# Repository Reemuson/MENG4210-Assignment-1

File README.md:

<h1 align="center">INPUT PROTECTION</h1>

<p align="center" width="100%">
  
</p>

***

<p align="center">
  
&nbsp; &nbsp; &nbsp; &nbsp;
  
</p>

***

## SPECIFICATIONS

| Parameter | Value | 
| --- | --- |
| Dimensions | 80.0 × 40.0 mm |

***

## DIRECTORY STRUCTURE

    .
    ├─ Computations       # Misc calculations
    ├─ HTML               # HTML files for generated webpage
    ├─ Images             # Pictures and renders
    │
    ├─ kibot_resources    # External resources for KiBot
    │  ├─ colors          # Color theme for KiCad
    │  ├─ fonts           # Fonts used in the project
    │  ├─ scripts         # External scripts used with KiBot
    │  └─ templates       # Templates for KiBot generated reports
    │
    ├─ kibot_yaml         # KiBot YAML config files
    ├─ KiRI               # KiRI (PCB diff viewer) files
    │
    ├─ lib                # KiCad footprint and symbol libraries
    │  ├─ 3d_models       # Component 3D models
    │  ├─ lib_fp          # Footprint libraries
    │  └─ lib_sym         # Symbol libraries
    │
    ├─ Logos              # Logos
    │
    ├─ Manufacturing      # Assembly and fabrication documents
    │  ├─ Assembly        # Assembly documents (BoM, pos, notes)
    │  │
    │  └─ Fabrication     # Fabrication documents (ZIP, notes)
    │     ├─ Drill Tables # CSV drill tables
    │     └─ Gerbers      # Gerbers
    │
    ├─ Report             # Reports for ERC/DRC
    ├─ Schematic          # PDF of schematic
    ├─ Templates          # Title block templates
    ├─ Testing
    │  └─ Testpoints      # Testpoints tables      
    │
    └─ Variants           # Outputs for assembly variants

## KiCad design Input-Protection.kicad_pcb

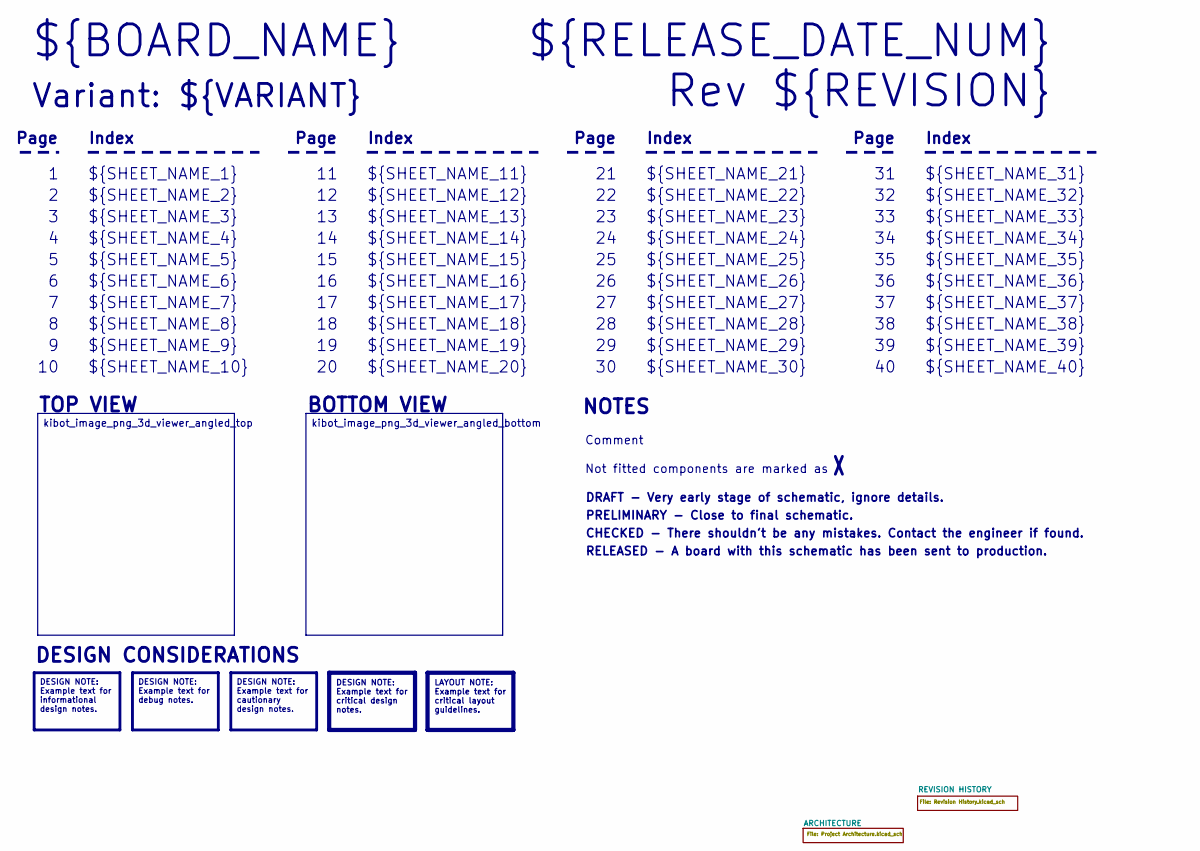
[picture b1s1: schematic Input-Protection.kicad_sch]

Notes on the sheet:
Variant: ${VARIANT}
RELEASED - A board with this schematic has been sent to production.
${SHEET_NAME_24}
Index
Page
PRELIMINARY - Close to final schematic.
${SHEET_NAME_22}
DRAFT - Very early stage of schematic, ignore details.
${SHEET_NAME_12}
${SHEET_NAME_8}
${SHEET_NAME_2}
${SHEET_NAME_5}
${SHEET_NAME_20}
${SHEET_NAME_23}
${RELEASE_DATE_NUM}
${SHEET_NAME_35}
Not fitted components are marked as
${SHEET_NAME_11}
${SHEET_NAME_6}
${SHEET_NAME_37}
${SHEET_NAME_26}
${SHEET_NAME_36}
Rev ${REVISION}
${SHEET_NAME_15}
CHECKED - There shouldn't be any mistakes. Contact the engineer if found.
BOTTOM VIEW
${SHEET_NAME_14}
${SHEET_NAME_21}
${SHEET_NAME_17}
${SHEET_NAME_18}
${SHEET_NAME_7}
${SHEET_NAME_31}
${BOARD_NAME}
NOTES
${SHEET_NAME_40}
${SHEET_NAME_39}
${SHEET_NAME_32}
${SHEET_NAME_1}
${SHEET_NAME_9}
${SHEET_NAME_38}

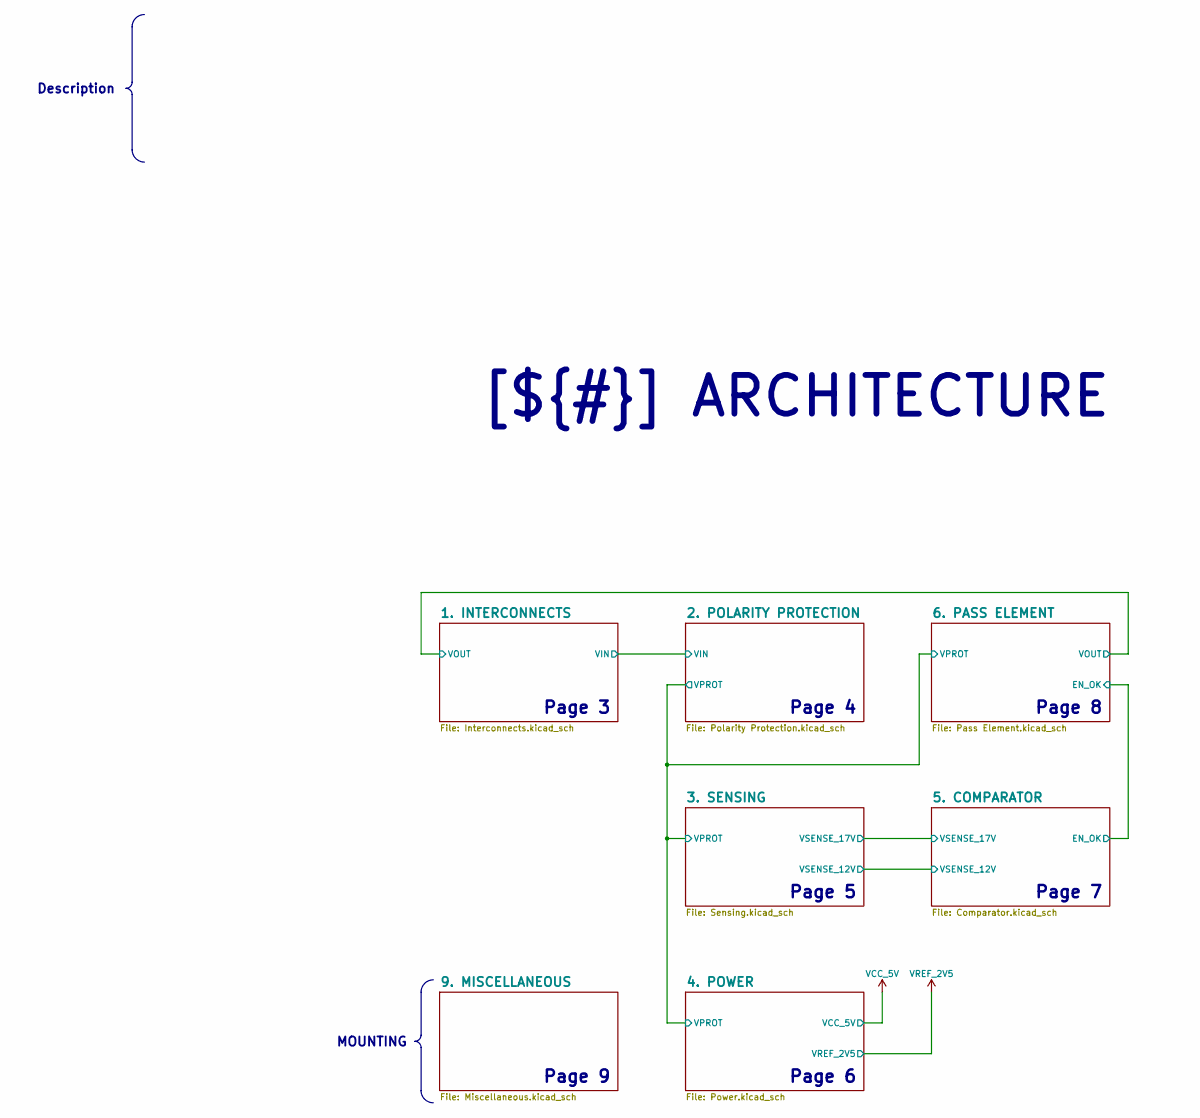
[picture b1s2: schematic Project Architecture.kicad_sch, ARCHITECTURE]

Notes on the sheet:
Page 7
Page 9
Page 3
Page 5
Page 8
Page 6
Page 4
Description
MOUNTING
[${#}] ${TITLE}

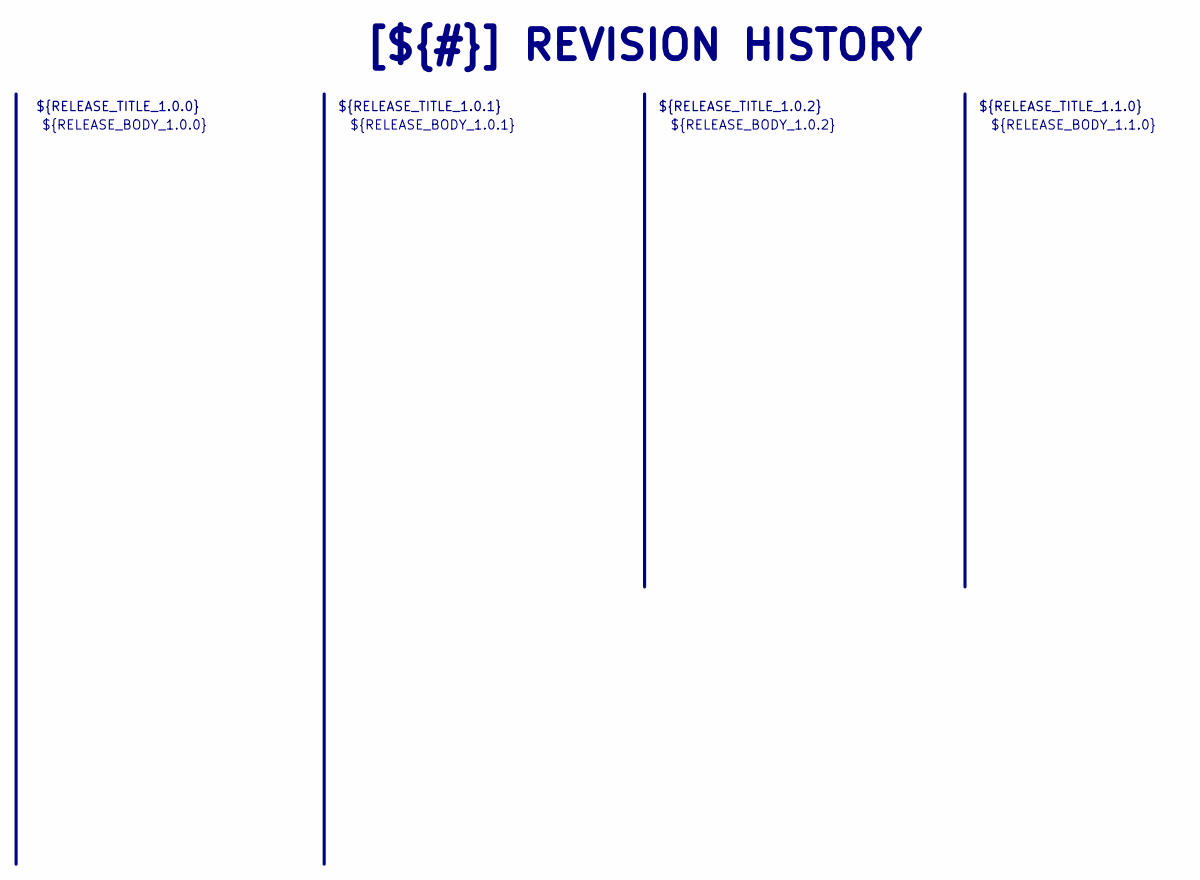
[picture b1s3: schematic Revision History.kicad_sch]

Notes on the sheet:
${RELEASE_BODY_1.1.0}
[${#}] ${TITLE}
${RELEASE_BODY_1.0.0}
${RELEASE_TITLE_1.0.2}
${RELEASE_BODY_1.0.2}
${RELEASE_BODY_1.0.1}
${RELEASE_TITLE_1.0.0}
${RELEASE_TITLE_1.0.1}
${RELEASE_TITLE_1.1.0}

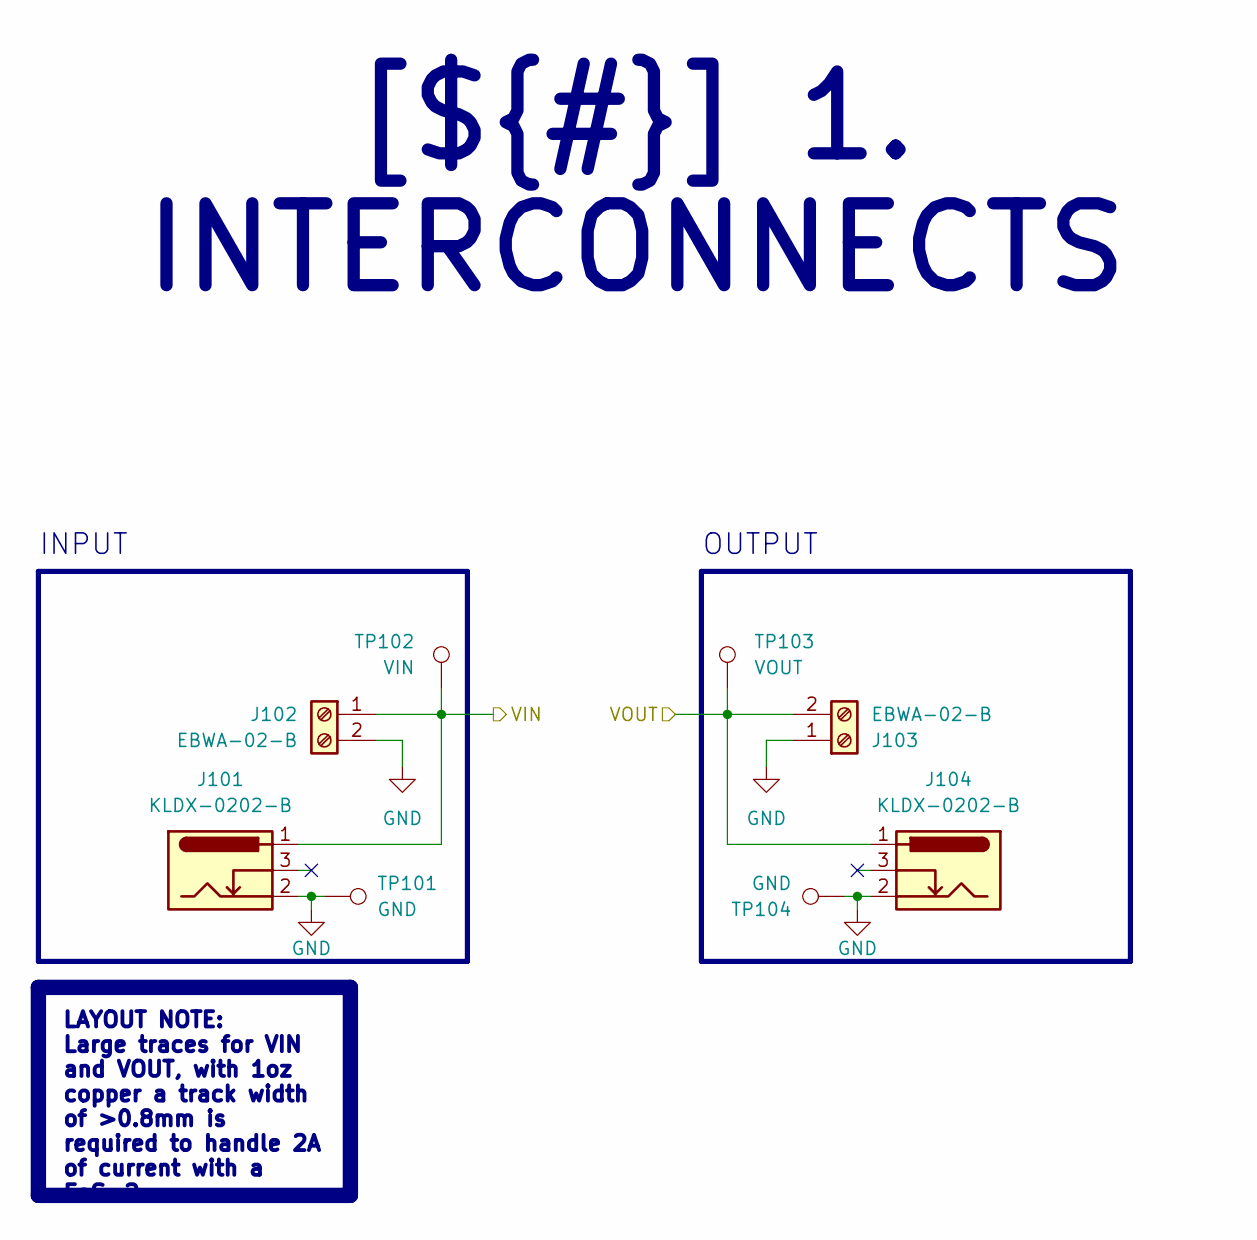
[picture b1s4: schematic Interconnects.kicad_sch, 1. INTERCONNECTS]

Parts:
J101: KLDX-0202-B; BarrelJack_Kycon_KLDX-0202-xC_Horizontal; MPN KLDX-0202-B
J102: EBWA-02-B; TerminalBlock_Phoenix_MKDS-1-2-3.81_1x02_P3.81mm_Horizontal; MPN EBWA-02-B
J103: EBWA-02-B; TerminalBlock_Phoenix_MKDS-1-2-3.81_1x02_P3.81mm_Horizontal
J104: KLDX-0202-B; BarrelJack_Kycon_KLDX-0202-xC_Horizontal
TP101, TP104: GND; TestPoint_THTPad_1.5x1.5mm_Drill0.7mm
TP102: VIN; TestPoint_Pad_D1.0mm
TP103: VOUT; TestPoint_Pad_D1.0mm

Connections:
/ARCHITECTURE/1. INTERCONNECTS/VIN: J101.1, J102.1, TP102.1; also elsewhere on the board
/ARCHITECTURE/1. INTERCONNECTS/VOUT: J103.2, J104.1, TP103.1; also elsewhere on the board
GND: J101.2, J102.2, J103.1, J104.2, TP101.1, TP104.1; also elsewhere on the board

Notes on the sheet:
INPUT
OUTPUT
LAYOUT NOTE: Large traces for VIN and VOUT, with 1oz copper a track width of >0.8mm is required to handle 2A of current with a FoS=2.
[${#}] ${TITLE}

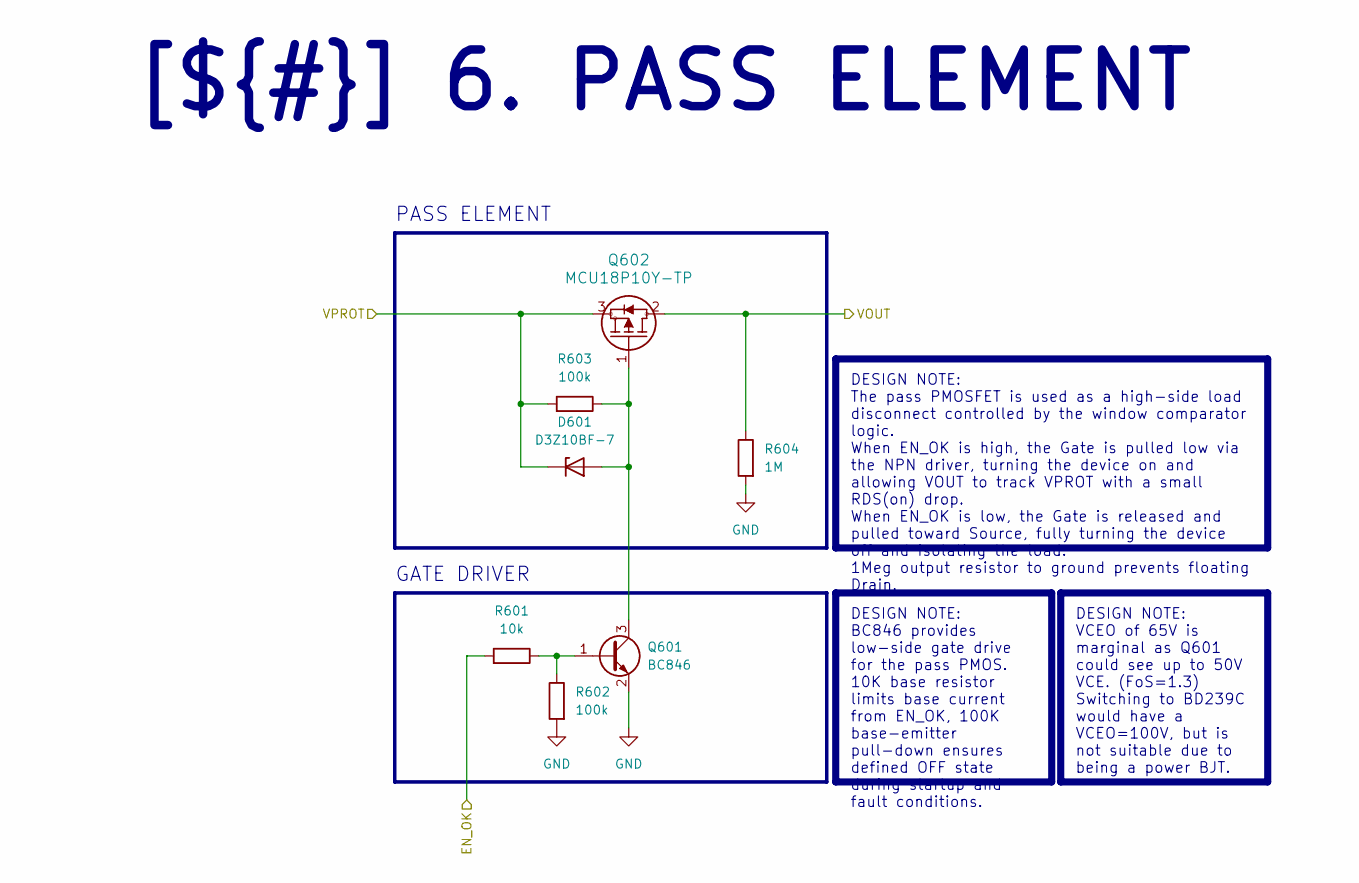
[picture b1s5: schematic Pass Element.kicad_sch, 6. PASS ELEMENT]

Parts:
D601: D3Z10BF-7; D_SOD-323_HandSoldering; MPN D3Z10BF-7
Q601: BC846; SOT-23; MPN BC846
Q602: MCU18P10Y-TP; DPAK_MCC; MPN MCU18P10Y-TP
R601: 10k; R_1206_3216Metric_Pad1.30x1.75mm_HandSolder
R602, R603: 100k; R_1206_3216Metric_Pad1.30x1.75mm_HandSolder
R604: 1M; R_1206_3216Metric_Pad1.30x1.75mm_HandSolder

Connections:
/ARCHITECTURE/1. INTERCONNECTS/VOUT: Q602.2, R604.1; also elsewhere on the board
/ARCHITECTURE/2. POLARITY PROTECTION/VPROT: D601.1 (K), Q602.3, R603.2; also elsewhere on the board
/ARCHITECTURE/5. COMPARATOR/EN_OK: R601.2; also elsewhere on the board
GND: Q601.2 (E), R602.2, R604.2; also elsewhere on the board
unnamed: D601.2 (A), Q601.3 (C), Q602.1, R603.1
unnamed: Q601.1 (B), R601.1, R602.1

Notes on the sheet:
PASS ELEMENT
GATE DRIVER
DESIGN NOTE: The pass PMOSFET is used as a high-side load disconnect controlled by the window comparator logic. When EN_OK is high, the Gate is pulled low via the NPN driver, turning the device on and allowing VOUT to track VPROT with a small RDS(on) drop. When EN_OK is low, the Gate is released an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
DESIGN NOTE: VCEO of 65V is marginal as Q601 could see up to 50V VCE. (FoS=1.3) Switching to BD239C would have a VCEO=100V, but is not suitable due to being a power BJT.
DESIGN NOTE: BC846 provides low-side gate drive for the pass PMOS. 10K base resistor limits base current from EN_OK, 100K base-emitter pull-down ensures defined OFF state during startup and fault conditions.
[${#}] ${TITLE}

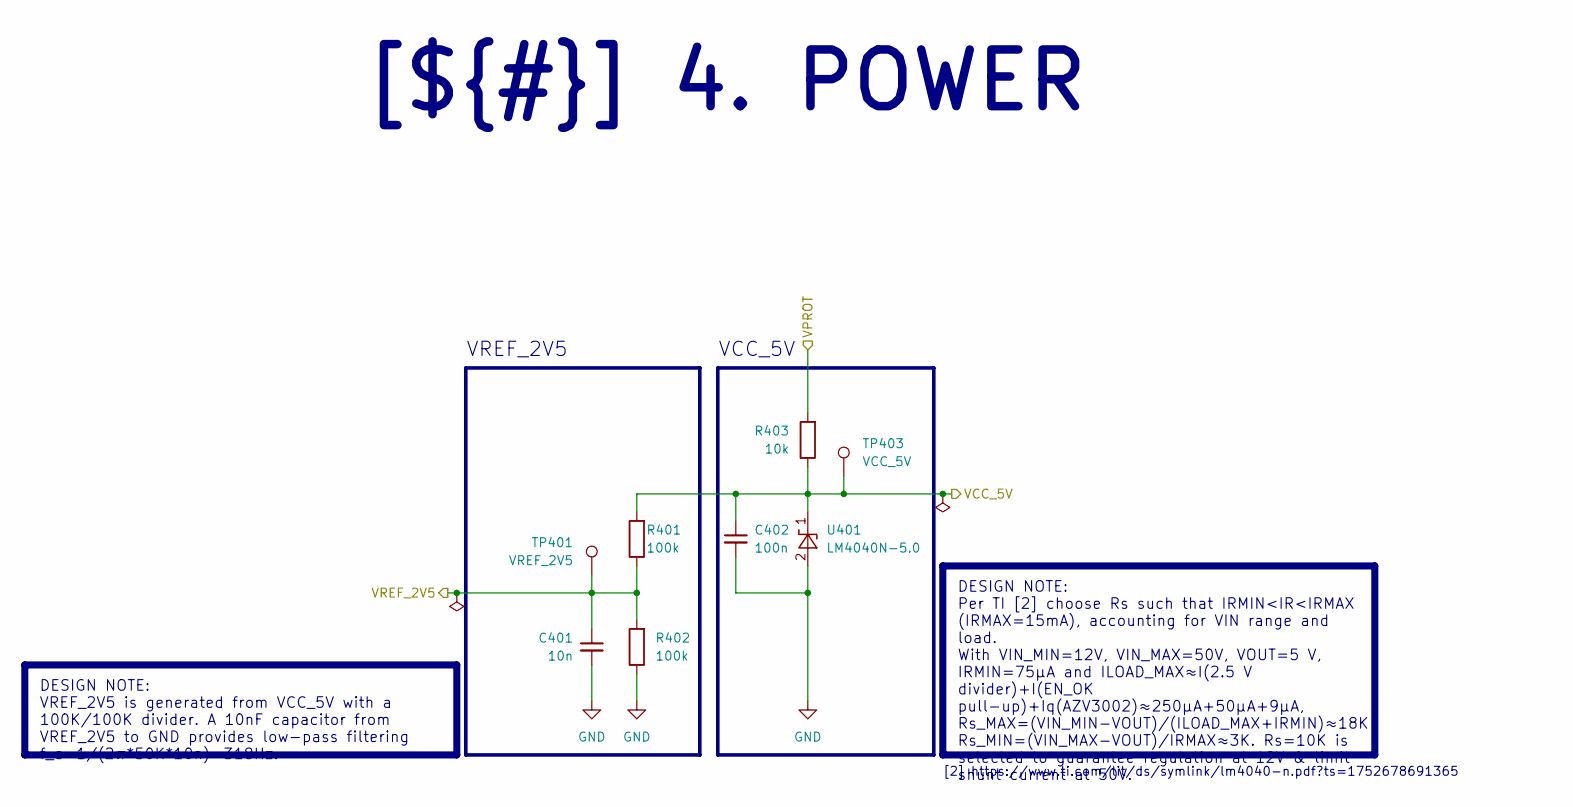
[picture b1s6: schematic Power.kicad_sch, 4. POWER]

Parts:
C401: 10n; C_0603_1608Metric_Pad1.08x0.95mm_HandSolder; Voltage_Rating 50V; Tolerance 10%; MPN C1608X7R1H103KT
C402: 100n; C_0603_1608Metric_Pad1.08x0.95mm_HandSolder; Voltage_Rating 16V; Tolerance 10%; MPN C1608X7R1C104KT
R401, R402: 100k; R_1206_3216Metric_Pad1.30x1.75mm_HandSolder
R403: 10k; R_1206_3216Metric_Pad1.30x1.75mm_HandSolder
TP401: VREF_2V5; TestPoint_Pad_D1.0mm
TP403: VCC_5V; TestPoint_Pad_D1.0mm
U401: LM4040N-5.0; SOT-23; MPN LM4040CIM3-5.0/NOPB

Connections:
/ARCHITECTURE/2. POLARITY PROTECTION/VPROT: R403.2; also elsewhere on the board
GND: C401.2, C402.2, R402.1, U401.2 (A); also elsewhere on the board
VCC_5V: C402.1, R401.2, R403.1, TP403.1, U401.1 (K); also elsewhere on the board
VREF_2V5: C401.1, R401.1, R402.2, TP401.1; also elsewhere on the board

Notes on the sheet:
VREF_2V5
VCC_5V
[2] https://www.ti.com/lit/ds/symlink/lm4040-n.pdf?ts=1752678691365
DESIGN NOTE: VREF_2V5 is generated from VCC_5V with a 100K/100K divider. A 10nF capacitor from VREF_2V5 to GND provides low-pass filtering f_c=1/(2π*50K*10n)=318Hz.
DESIGN NOTE: Per TI [2] choose Rs such that IRMIN<IR<IRMAX (IRMAX=15mA), accounting for VIN range and load. With VIN_MIN=12V, VIN_MAX=50V, VOUT=5 V, IRMIN=75µA and ILOAD_MAX≈I(2.5 V divider)+I(EN_OK pull-up)+Iq(AZV3002)≈250µA+50µA+9µA, Rs_MAX=(VIN_MIN−VOUT)/(ILOAD_MAX+IRMIN)≈18K Rs_MIN=(VIN_MAX−VOU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
[${#}] ${TITLE}

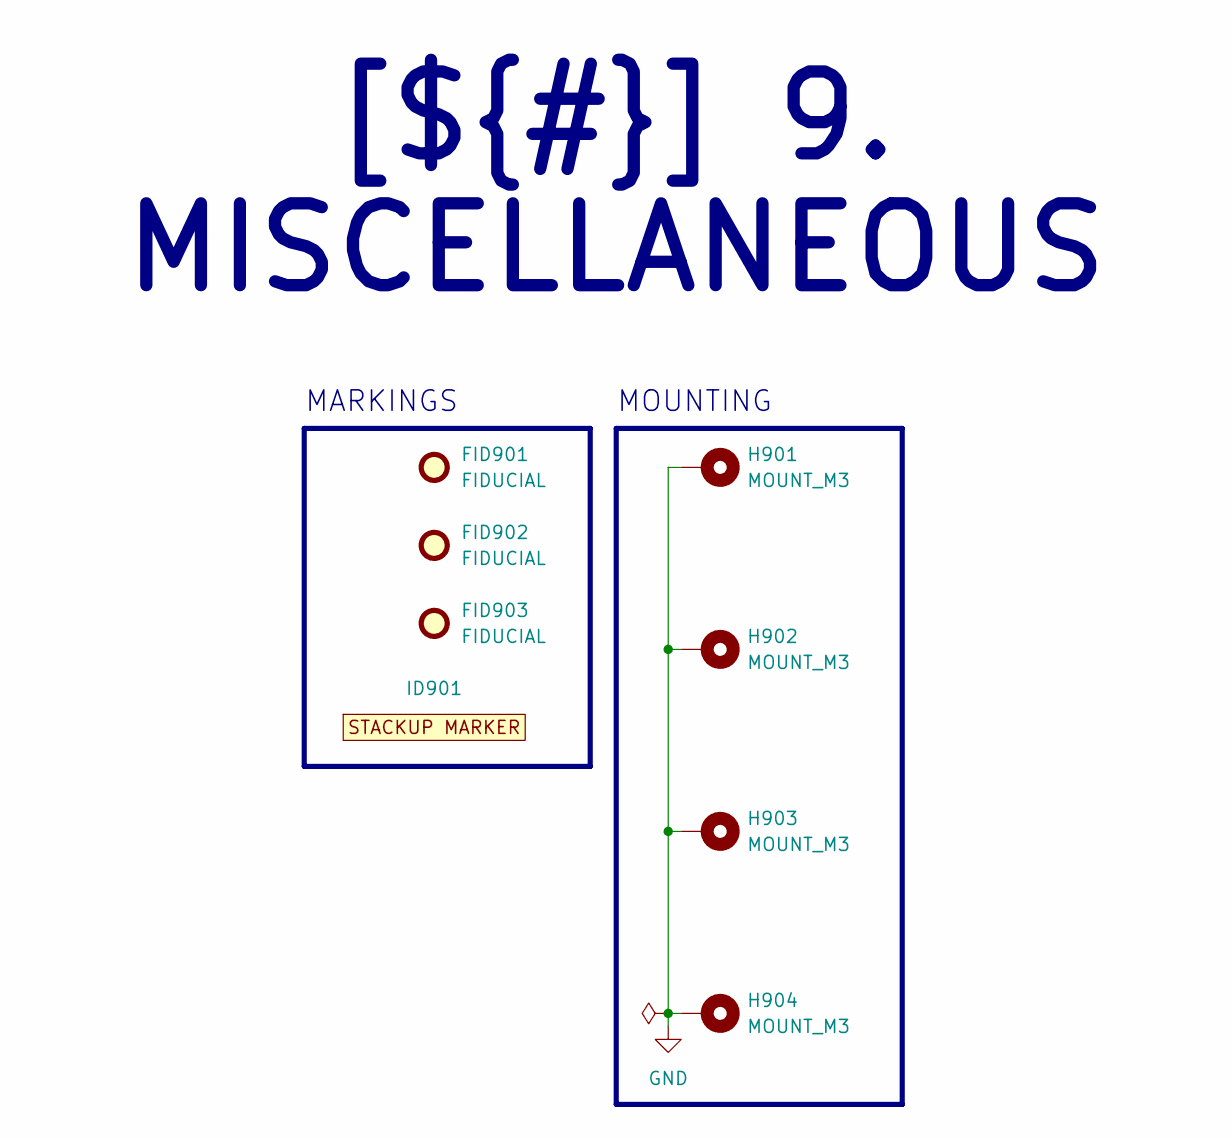
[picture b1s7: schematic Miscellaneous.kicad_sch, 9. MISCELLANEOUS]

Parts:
FID901, FID902, FID903: FIDUCIAL; Fiducial_Cross_0.5mm_Mask2mm
H901, H902, H903, H904: MOUNT_M3; MountingHole_3.2mm_M3_ISO7380_Pad
ID901: BOARD_STACKUP_MARKER; STACKUP_ID_2L_SML

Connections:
GND: H901.1, H902.1, H903.1, H904.1; also elsewhere on the board

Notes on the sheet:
MOUNTING
MARKINGS
[${#}] ${TITLE}

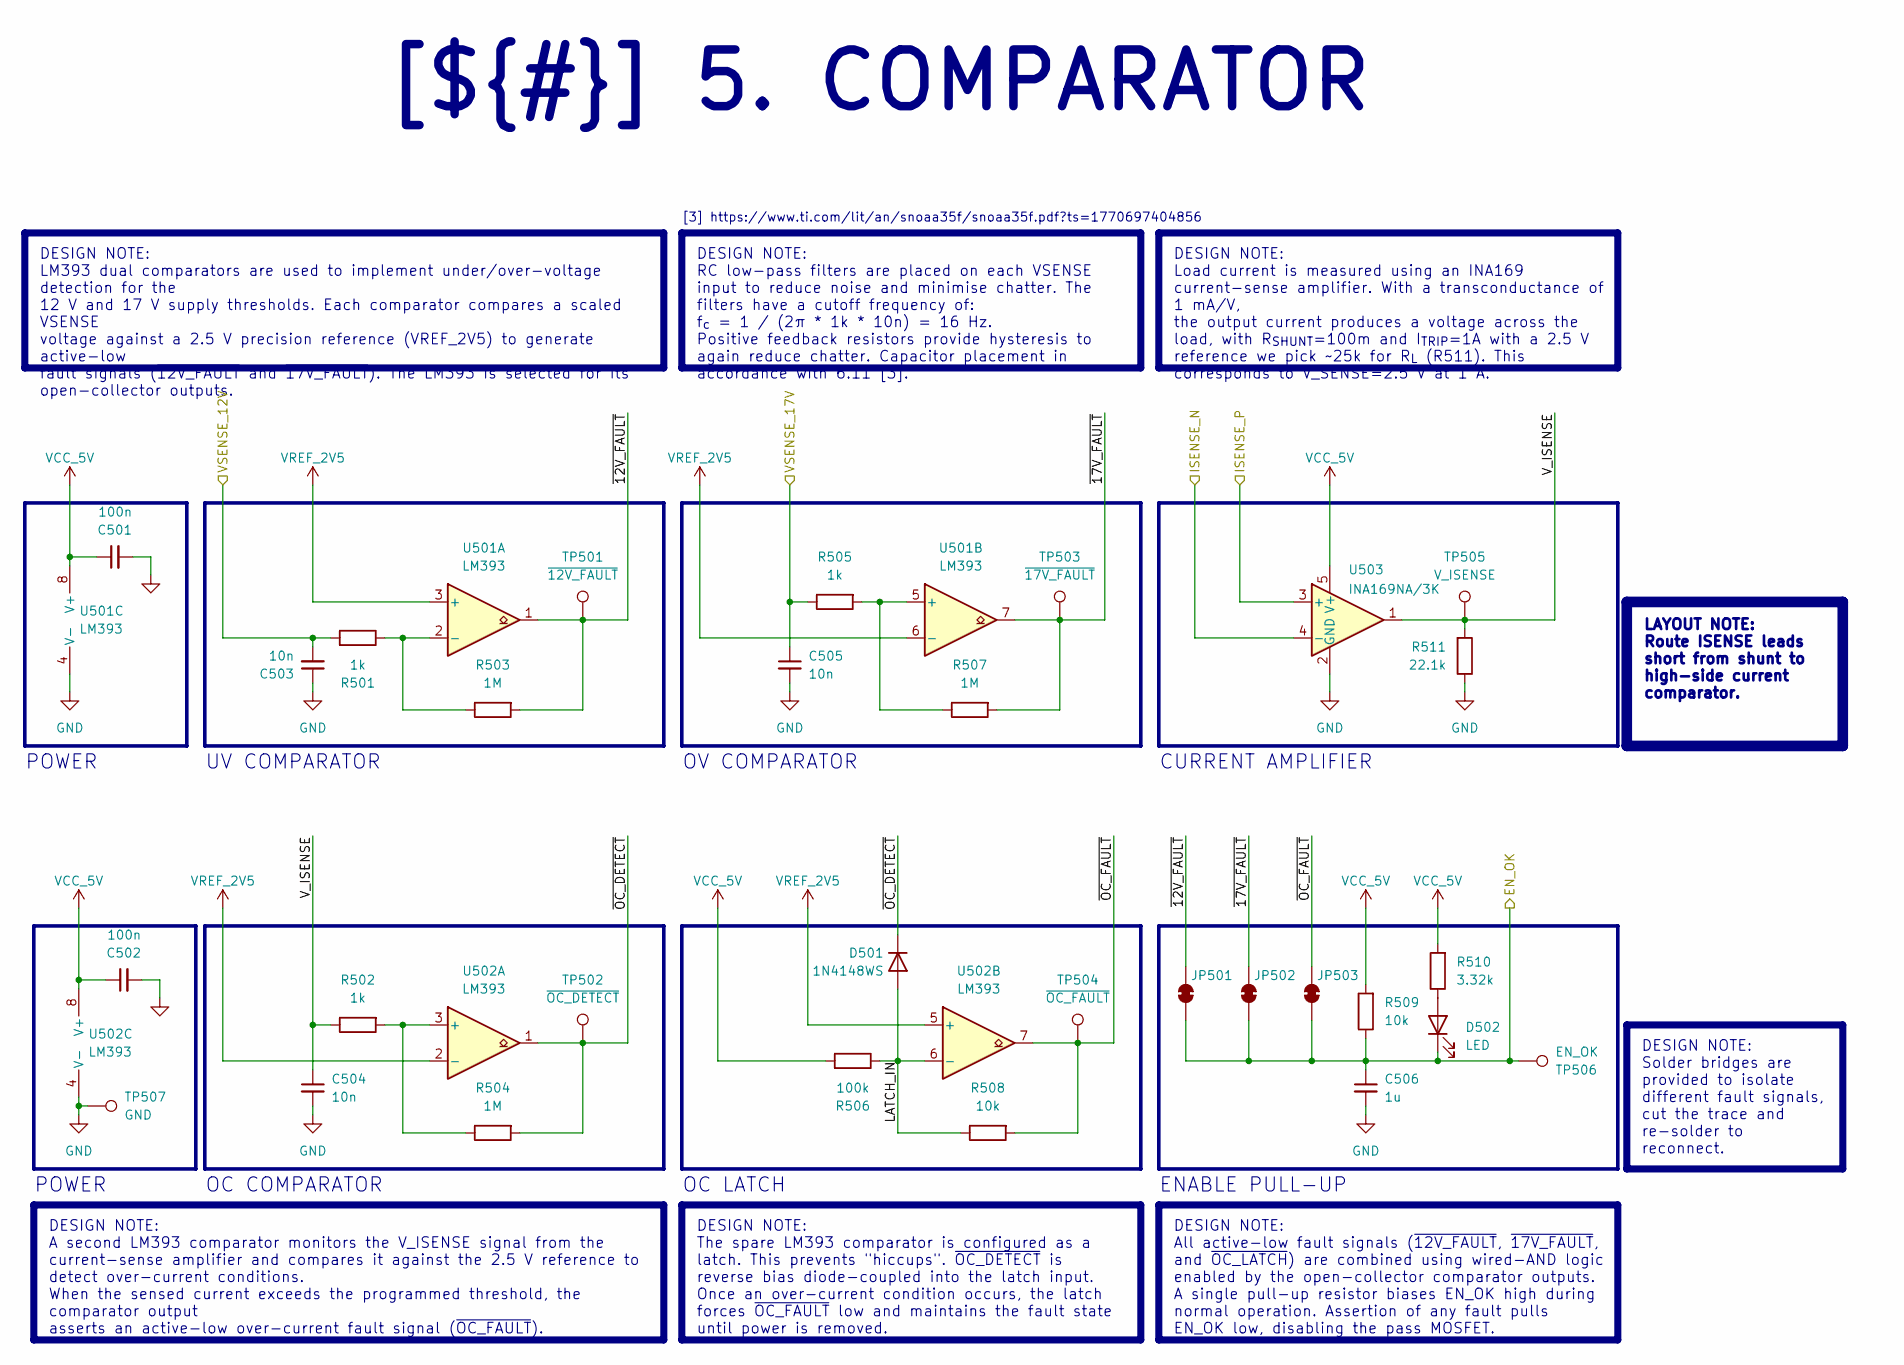
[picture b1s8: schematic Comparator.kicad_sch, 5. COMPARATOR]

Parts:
C501, C502: 100n; C_0603_1608Metric_Pad1.08x0.95mm_HandSolder; Voltage_Rating 16V; Tolerance 10%; MPN C1608X7R1C104KT
C503, C504, C505: 10n; C_0603_1608Metric_Pad1.08x0.95mm_HandSolder; Voltage_Rating 50V; Tolerance 10%; MPN C1608X7R1H103KT
C506: 1u; C_0603_1608Metric_Pad1.08x0.95mm_HandSolder; Voltage_Rating 6.3V; Tolerance 10%; MPN C1608X5R0J105KT
D501: 1N4148WS; D_SOD-323; MPN 1N4148WS
D502: LED; LED_0805_2012Metric_Pad1.15x1.40mm_HandSolder; MPN LTST-C170KRKT
JP501, JP502, JP503: SolderJumper_2_Bridged; SolderJumper-2_P1.3mm_Bridged_Pad1.0x1.5mm
R501, R502, R505: 1k; R_1206_3216Metric_Pad1.30x1.75mm_HandSolder
R503, R504, R507: 1M; R_1206_3216Metric_Pad1.30x1.75mm_HandSolder
R506: 100k; R_1206_3216Metric_Pad1.30x1.75mm_HandSolder
R508, R509: 10k; R_1206_3216Metric_Pad1.30x1.75mm_HandSolder
R510: 3.32k; R_1206_3216Metric_Pad1.30x1.75mm_HandSolder
R511: 22.1k; R_1206_3216Metric_Pad1.30x1.75mm_HandSolder
TP501: ~{12V_FAULT}; TestPoint_Pad_D1.0mm
TP502: ~{OC_DETECT}; TestPoint_Pad_D1.0mm
TP503: ~{17V_FAULT}; TestPoint_Pad_D1.0mm
TP504: ~{OC_FAULT}; TestPoint_Pad_D1.0mm
TP505: V_ISENSE; TestPoint_Pad_D1.0mm
TP506: EN_OK; TestPoint_Pad_D1.0mm
TP507: GND; TestPoint_THTPad_1.5x1.5mm_Drill0.7mm
U501, U502: LM393; SOIC-8_3.9x4.9mm_P1.27mm; MPN LM393ADT
U503: INA169NA/3K; SOT-23-5; MPN INA169NA/3K

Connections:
/ARCHITECTURE/2. POLARITY PROTECTION/VPROT: U503.3 (+); also elsewhere on the board
/ARCHITECTURE/3. SENSING/ISENSE_N: U503.4 (-); also elsewhere on the board
/ARCHITECTURE/3. SENSING/VSENSE_12V: C503.2, R501.2; also elsewhere on the board
/ARCHITECTURE/3. SENSING/VSENSE_17V: C505.1, R505.1; also elsewhere on the board
/ARCHITECTURE/5. COMPARATOR/EN_OK: C506.1, D502.1 (K), JP501.1 (A), JP502.1 (A), JP503.1 (A), R509.1, TP506.1; also elsewhere on the board
/ARCHITECTURE/5. COMPARATOR/LATCH_IN: D501.2 (A), R506.1, R508.1, U502.6 (-)
/ARCHITECTURE/5. COMPARATOR/V_ISENSE: C504.1, R502.1, R511.2, TP505.1, U503.1
/ARCHITECTURE/5. COMPARATOR/~12V_FAULT: JP501.2 (B), R503.2, TP501.1, U501.1
/ARCHITECTURE/5. COMPARATOR/~17V_FAULT: JP502.2 (B), R507.2, TP503.1, U501.7
/ARCHITECTURE/5. COMPARATOR/~OC_DETECT: D501.1 (K), R504.2, TP502.1, U502.1
/ARCHITECTURE/5. COMPARATOR/~OC_FAULT: JP503.2 (B), R508.2, TP504.1, U502.7
GND: C501.2, C502.2, C503.1, C504.2, C505.2, C506.2, R511.1, TP507.1, U501.4 (V-), U502.4 (V-), U503.2 (GND); also elsewhere on the board
unnamed: D502.2 (A), R510.1
unnamed: R501.1, R503.1, U501.2 (-)
unnamed: R505.2, R507.1, U501.5 (+)
unnamed: R502.2, R504.1, U502.3 (+)
VCC_5V: C501.1, C502.1, R506.2, R509.2, R510.2, U501.8 (V+), U502.8 (V+), U503.5 (V+); also elsewhere on the board
VREF_2V5: U501.3 (+), U501.6 (-), U502.2 (-), U502.5 (+); also elsewhere on the board

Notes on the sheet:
OV COMPARATOR
OC COMPARATOR
UV COMPARATOR
ENABLE PULL-UP
[3] https://www.ti.com/lit/an/snoaa35f/snoaa35f.pdf?ts=1770697404856
POWER
OC LATCH
CURRENT AMPLIFIER
DESIGN NOTE: Solder bridges are provided to isolate different fault signals, cut the trace and re-solder to reconnect.
DESIGN NOTE: RC low-pass filters are placed on each VSENSE input to reduce noise and minimise chatter. The filters have a cutoff frequency of: f_{c} = 1 / (2π * 1k * 10n) = 16 Hz. Positive feedback resistors provide hysteresis to again reduce chatter. Capacitor placement in accordance with 6.11 [3].
LAYOUT NOTE: Route ISENSE leads short from shunt to high-side current comparator.
DESIGN NOTE: All active-low fault signals (~{12V_FAULT}, ~{17V_FAULT}, and ~{OC_LATCH}) are combined using wired-AND logic enabled by the open-collector comparator outputs. A single pull-up resistor biases EN_OK high during normal operation. Assertion of any fault pulls EN_OK low, disabling the pas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
DESIGN NOTE: Load current is measured using an INA169 current-sense amplifier. With a transconductance of 1 mA/V, the output current produces a voltage across the load, with R_{SHUNT}=100m and I_{TRIP}=1A with a 2.5 V reference we pick ~25k for R_{L} (R511). This corresponds to V_SENSE=2.5 V at 1 A.
DESIGN NOTE: A second LM393 comparator monitors the V_ISENSE signal from the current-sense amplifier and compares it against the 2.5 V reference to detect over-current conditions. When the sensed current exceeds the programmed threshold, the comparator output asserts an active-low over-current faul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
DESIGN NOTE: LM393 dual comparators are used to implement under/over-voltage detection for the 12 V and 17 V supply thresholds. Each comparator compares a scaled VSENSE voltage against a 2.5 V precision reference (VREF_2V5) to generate active-low fault signals (~{12V_FAULT} and ~{17V_FAULT}). The L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
DESIGN NOTE: The spare LM393 comparator is configured as a latch. This prevents "hiccups". ~{OC_DETECT} is reverse bias diode-coupled into the latch input. Once an over-current condition occurs, the latch forces ~{OC_FAULT} low and maintains the fault state until power is removed.
[${#}] ${TITLE}

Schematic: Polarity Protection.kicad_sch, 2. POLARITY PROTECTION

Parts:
D201: D3Z10BF-7; D_SOD-323_HandSoldering; MPN D3Z10BF-7
Q201: MCU18P10Y-TP; DPAK_MCC; MPN MCU18P10Y-TP
R201, R202: 100k; R_1206_3216Metric_Pad1.30x1.75mm_HandSolder
TP201: VPROT; TestPoint_Pad_D1.5mm

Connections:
/ARCHITECTURE/1. INTERCONNECTS/VIN: Q201.2; also elsewhere on the board
/ARCHITECTURE/2. POLARITY PROTECTION/VPROT: D201.1 (K), Q201.3, R202.2, TP201.1; also elsewhere on the board
GND: R201.1; also elsewhere on the board
unnamed: D201.2 (A), Q201.1, R201.2, R202.1

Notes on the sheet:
[1] https://www.ti.com/lit/an/slvae57b/slvae57b.pdf?ts=1770319054914
DESIGN NOTE: This PMOSFET is acting as an ideal diode [1]. 10V zener from Gate to Source to limit VGS <= 10V under all VIN and transient conditions to protect PMOSFET. 100K Gate to Source resistor to not allow floating Gate. 100K Gate pulldown resistor so Gate is off and not affected by leakage or 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
LAYOUT NOTE: Large traces for VPROT, with 1oz copper a track width of >0.8mm is required to handle 2A of current with a FoS=2.
[${#}] ${TITLE}

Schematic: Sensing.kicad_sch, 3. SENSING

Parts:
R301: 100m; R_1206_3216Metric_Pad1.30x1.75mm_HandSolder; Manufacturer Part Number KDV12FR100ET
R302: 39.2k; R_1206_3216Metric_Pad1.30x1.75mm_HandSolder
R303, R305: 10k; R_1206_3216Metric_Pad1.30x1.75mm_HandSolder
R304: 56.2k; R_1206_3216Metric_Pad1.30x1.75mm_HandSolder
TP301: GND; TestPoint_THTPad_1.5x1.5mm_Drill0.7mm
TP302: VSENSE_12V; TestPoint_Pad_D1.0mm
TP303: VSENSE_17V; TestPoint_Pad_D1.0mm

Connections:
/ARCHITECTURE/2. POLARITY PROTECTION/VPROT: R301.2; also elsewhere on the board
/ARCHITECTURE/3. SENSING/ISENSE_N: R301.1, R302.2, R304.2; also elsewhere on the board
/ARCHITECTURE/3. SENSING/VSENSE_12V: R302.1, R303.2, TP302.1; also elsewhere on the board
/ARCHITECTURE/3. SENSING/VSENSE_17V: R304.1, R305.2, TP303.1; also elsewhere on the board
GND: R303.1, R305.1, TP301.1; also elsewhere on the board

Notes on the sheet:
SHUNT
UV CONDITION
OV CONDITION
DESIGN NOTE: At VPROT = 17 V, the divider current is approximately I_{DIV} = VPROT / (R_{TOP} + R_{BOT}) = 17 V / 68k = 250 uA, Which is sufficient for the input bias of the comparators.
DESIGN NOTE: The over-current trip point is set to I_{TRIP} = 1 A. With a shunt resistor value of R_{SHUNT} = 100m, the differential shunt voltage at the trip point is: V_{SENSE} = I * R_{SHUNT} = 1 A * 100m = 100 mV.
DESIGN NOTE: R_{BOT} is chosen as 10k to provide a low-impedance sense node with reasonable divider current. Solving for R_{TOP} gives: R_{TOP} = R_{BOT} * (V_{TRIP} / VREF_2V5 − 1) With VREF_2V5 = 2.5 V and RBOT = 10k: For V_{TRIP} = 12 V: R_{TOP} = 10k * (12 / 2.5 − 1) = 38k For V_{TRIP} = 17 V: 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
DESIGN NOTE: The protected input voltage VPROT is scaled to sense voltage VSENSE using a divider for comparison against VREF_2V5. VSENSE = VPROT * R_{BOT} / (R_{TOP} + R_{BOT}) The comparator trips when VSENSE = VREF_2V5, giving a trip voltage of V_{TRIP} = VREF_2V5 * (R_{TOP} + R_{BOT}) / R_{BOT}.
[${#}] ${TITLE}

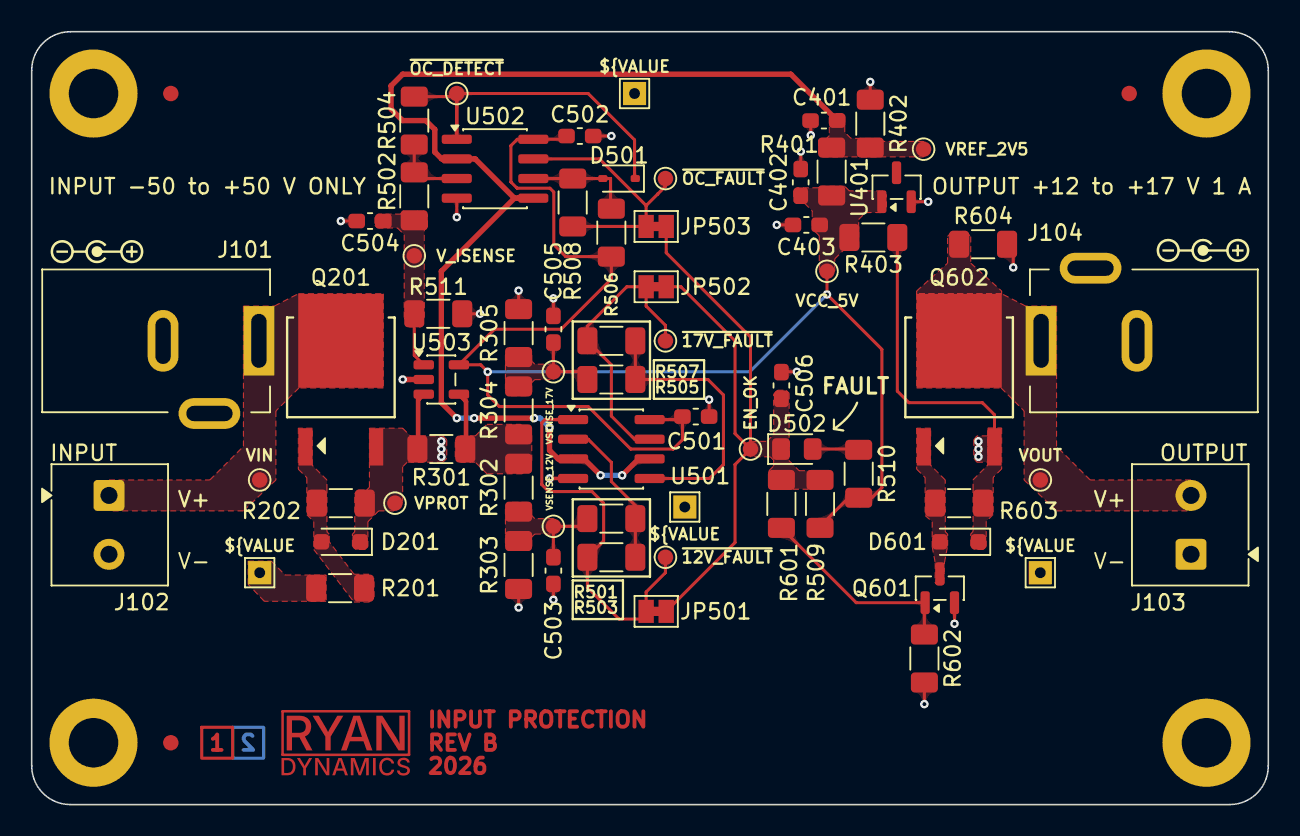
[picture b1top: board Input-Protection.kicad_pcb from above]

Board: 2 copper layers, 80.0 x 50.0 mm, 77 parts (0 on the bottom side), 23 nets.

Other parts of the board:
C403: 100n; C_0603_1608Metric_Pad1.08x0.95mm_HandSolder
TP402: VCC_5V; TestPoint_Pad_D1.0mm

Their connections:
GND: C403.2; also elsewhere on the board
VCC_5V: C403.1, TP402.1; also elsewhere on the board

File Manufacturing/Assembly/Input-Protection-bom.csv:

Row,Quantity Per PCB,References,Value,Datasheet,Footprint,Description,Manufacturer,MPN,Supplier,Supplier Part Number,Notes
1,4,C401 C503 C504 C505,10n,https://mm.digikey.com/Volume0/opasdata/d220001/medias/docus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,C_0603_1608Metric_Pad1.08x0.95mm_HandSolder,CAP CER 0.01UF 50V X7R 0603,TPK,C1608X7R1H103KT,,,
2,3,C403 C501 C502,100n,https://mm.digikey.com/Volume0/opasdata/d220001/medias/docus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,C_0603_1608Metric_Pad1.08x0.95mm_HandSolder,CAP CER 0.1UF 16V X7R 0603,TPK,C1608X7R1C104KT,,,
3,2,C402 C506,1u,https://mm.digikey.com/Volume0/opasdata/d220001/medias/docus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,C_0603_1608Metric_Pad1.08x0.95mm_HandSolder,CAP CER 1UF 50V X7R 0603,TPK,C1608X5R0J105KT,,,
4,1,D501,1N4148WS,https://diotec.com/request/datasheet/1n4148ws.pdf,D_SOD-323,DIODE STANDARD 75V 150MA SOD323F,Diotec Semiconductor,1N4148WS,,,"Fast switching diode, low leakage, used for diode-AND logic gating of control signals"
5,2,D201 D601,D3Z10BF-7,https://www.diodes.com/assets/Datasheets/D3ZxVxBF.pdf,D_SOD-323_HandSoldering,DIODE ZENER 10V 400MW SOD323F,Diodes Incorporated,D3Z10BF-7,,,"VZ = 10 V, suitable for input over-voltage clamping"
6,1,D502,LED,https://optoelectronics.liteon.com/upload/download/DS-22-99-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,LED_0805_2012Metric_Pad1.15x1.40mm_HandSolder,LED RED CLEAR SMD,Lite-On Inc.,LTST-C170KRKT,,,Any low power red 0805 LED
7,2,J102 J103,EBWA-02-B,https://app.adam-tech.com/products/download/data_sheet/20424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,TerminalBlock_Phoenix_MKDS-1-2-3.81_1x02_P3.81mm_Horizontal,EURO BLOCK 2P,Adam Tech,EBWA-02-B,,,
8,2,J101 J104,KLDX-0202-B,https://www.kycon.com/Catalog_PDF/KLDX_0202.pdf,BarrelJack_Kycon_KLDX-0202-xC_Horizontal,CONN PWR JACK 2.5X5.5MM SOLDER,Kycon Inc,KLDX-0202-B,,,
9,1,Q601,BC846,https://assets.nexperia.com/documents/data-sheet/BC846X-Q_SER.pdf,SOT-23,TRANS NPN 65V 0.1A TO-236AB,Nexperia USA Inc.,BC846,,,"VCEO > 65 V for 50 V rail, IC small, used as gate pull-down switch"
10,2,Q201 Q602,MCU18P10Y-TP,https://www.mccsemi.com/pdf/Products/MCU18P10Y(DPAK).pdf,DPAK_MCC,MOSFET P-CH 100V 18A DPAK,MCC (Micro Commercial Components),MCU18P10Y-TP,,,"VDS > 100 V, ID > 2 A, P-channel device suitable for high-side switching"
11,1,R301,100m,https://www.ohmite.com/assets/images/res-kdv.pdf,R_1206_3216Metric_Pad1.30x1.75mm_HandSolder,RES 0.1 OHM 1% 1/2W 1206,Ohmite,,,,"Current sense shunt, sets OCP trip (~1 A). Ideally should be <100m"
12,3,R501 R502 R505,1k,https://www.analogtechnologies.com/document/New_Resistor_Kits.pdf,R_1206_3216Metric_Pad1.30x1.75mm_HandSolder,RES 1K OHM 1% 1/4W 1206,Analog Technologies,,,,
13,2,R403 R510,3.32k,https://www.analogtechnologies.com/document/New_Resistor_Kits.pdf,R_1206_3216Metric_Pad1.30x1.75mm_HandSolder,RES 3.32K OHM 1% 1/4W 1206,Analog Technologies,,,,
14,5,R303 R305 R508 R509 R601,10k,https://www.analogtechnologies.com/document/New_Resistor_Kits.pdf,R_1206_3216Metric_Pad1.30x1.75mm_HandSolder,RES 10K OHM 1% 1/4W 1206,Analog Technologies,,,,
15,1,R511,22.1k,https://www.analogtechnologies.com/document/New_Resistor_Kits.pdf,R_1206_3216Metric_Pad1.30x1.75mm_HandSolder,RES 22.1K OHM 1% 1/4W 1206,Analog Technologies,,,,
16,1,R302,39.2k,https://www.analogtechnologies.com/document/New_Resistor_Kits.pdf,R_1206_3216Metric_Pad1.30x1.75mm_HandSolder,RES 39.2K OHM 1% 1/4W 1206,Analog Technologies,,,,
17,1,R304,56.2k,https://www.analogtechnologies.com/document/New_Resistor_Kits.pdf,R_1206_3216Metric_Pad1.30x1.75mm_HandSolder,RES 56.2K OHM 1% 1/4W 1206,Analog Technologies,,,,
18,7,R201 R202 R401 R402 R506 R602 R603,100k,https://www.analogtechnologies.com/document/New_Resistor_Kits.pdf,R_1206_3216Metric_Pad1.30x1.75mm_HandSolder,RES 100K OHM 1% 1/4W 1206,Analog Technologies,,,,
19,4,R503 R504 R507 R604,1M,https://www.analogtechnologies.com/document/New_Resistor_Kits.pdf,R_1206_3216Metric_Pad1.30x1.75mm_HandSolder,RES 1M OHM 1% 1/4W 1206,Analog Technologies,,,,
20,1,U503,INA169NA/3K,http://www.ti.com/lit/ds/symlink/ina169.pdf,SOT-23-5,IC CURRENT MONITOR 0.5% SOT23-5,Texas Instruments,INA169NA/3K,,,Transconductance of 1mA/V
21,2,U501 U502,LM393,http://www.ti.com/lit/ds/symlink/lm393.pdf,SOIC-8_3.9x4.9mm_P1.27mm,IC COMPARATOR 2 GEN PUR 8SOIC,Texas Instruments,LM393ADT,,,"Open-collector output required, >5V tolerant inputs."
22,1,U401,LM4040N-5.0,http://www.ti.com/lit/ds/symlink/lm4040-n.pdf,SOT-23,IC VREF SHUNT 0.5% SOT23-3,Texas Instruments,LM4040CIM3-5.0/NOPB,,,"VREF = 5.0 V, low temperature coefficient, suitable for precision threshold VREF"

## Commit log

2026-02-06 feat: schematic mvp
2026-02-06 fix: reset pcb layout
2026-02-06 Update Outputs
2026-02-07 feat: Added some design notes, fixed some values in line with sim
2026-02-07 fix: roll back config changes to defaults
2026-02-07 fix: fix properties of actives with MPN
2026-02-07 fix: template changes
2026-02-07 fix: test font change from TNR to KiCad
2026-02-09 feat: preliminary pcb layout
2026-02-09 fix: template issue
2026-02-09 fix: test point changes
2026-02-09 fix: bom improvements & more notes
2026-02-09 feat: ERC/DRC checks
2026-02-10 feat!: added OC protection, redesigned board from near scratch, size increase
2026-02-10 fix: adjust keying for images
2026-02-10 fix: fab layer clean up and bom additions
2026-02-11 feat: revision A release
2026-02-11 Update CHANGELOG
2026-02-11 Update Outputs (release)
2026-02-18 feat: revision B release
2026-02-18 docs: prepare Unreleased for 1.1.0
